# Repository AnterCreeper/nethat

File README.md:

# Dual Gigabit Ethernet HAT

If any questions, welcome for Issues & PRs   
如果有疑问，欢迎提交Issues或PR

**WARNING! This Project is not been fully productive tested, use at your own risk!**   
**警告！该项目未经充分的生产测试，使用需要你自己衡量**

### License

This project is licensed under the LGPL-2.1-or-later license. **DO NOT** download or clone this project until you have read and agree the LICENSE.     
该项目采用 `LGPL-2.1 以及之后版本` 授权。当你下载或克隆项目时，默认已经阅读并同意该协定。

### TODO
1. Should we add one EEPROM?

### Overview

This Project contains two `RTL8211F-CG` chips which is used to explore and demonstrate FPGA Ethernet application. This Project is compatible with [CUBE](https://github.com/AnterCreeper/CUBE) FPGA Devkit.  
该项目包含两个 `RTL8211F-CG` 芯片, 用于探索和展示基于 FPGA 的以太网应用。该项目与 [CUBE](https://github.com/AnterCreeper/CUBE) 开发工具搭配。

The PCB takes 4 layers JLC04161H-3313 Stacking, 1.6mm Thickness.
PCB 采用 4 层 JLC04161H-3313 叠层, 1.6mm 厚度。

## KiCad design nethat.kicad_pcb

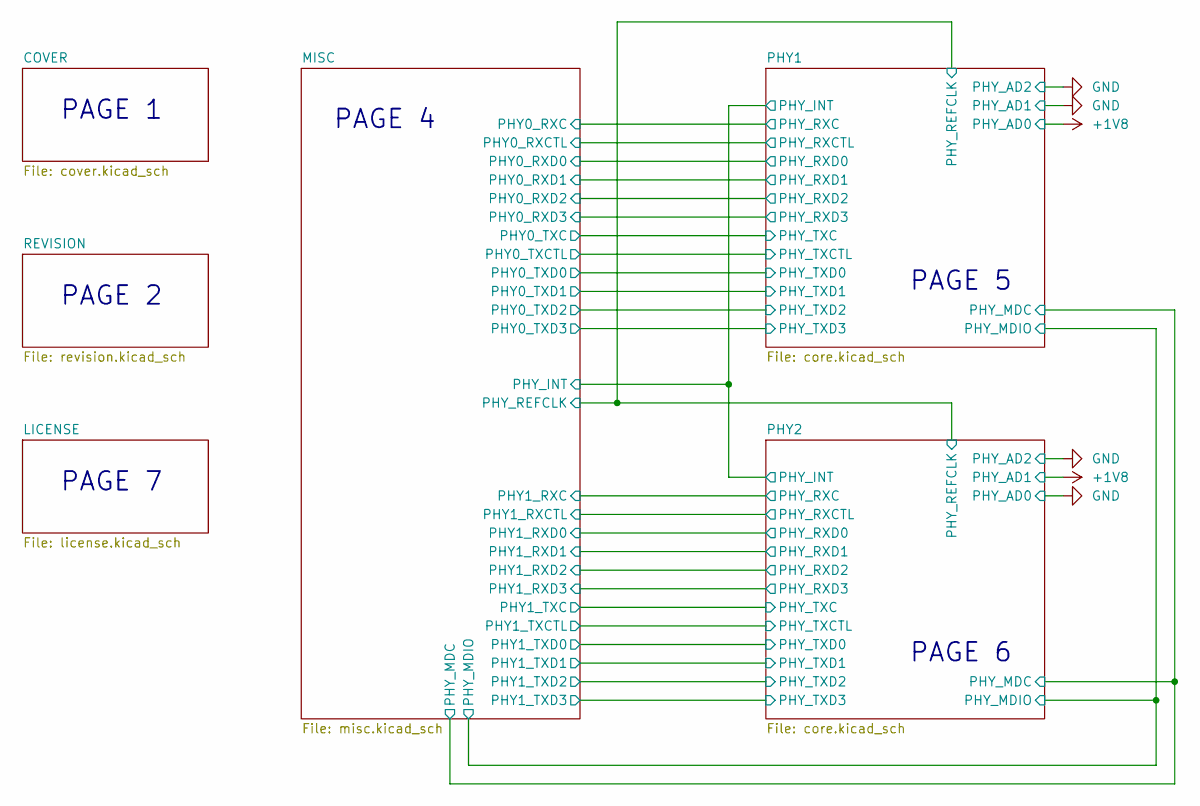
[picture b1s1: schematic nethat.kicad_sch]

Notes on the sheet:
PAGE 4
PAGE 1
PAGE 6
PAGE 2
PAGE 7
PAGE 5

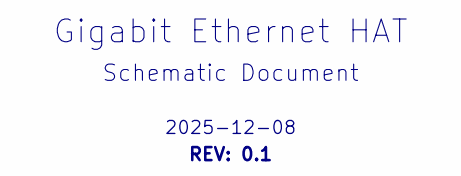
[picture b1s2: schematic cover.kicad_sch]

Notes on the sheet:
REV: 0.1
2025-12-08
Gigabit Ethernet HAT
Schematic Document

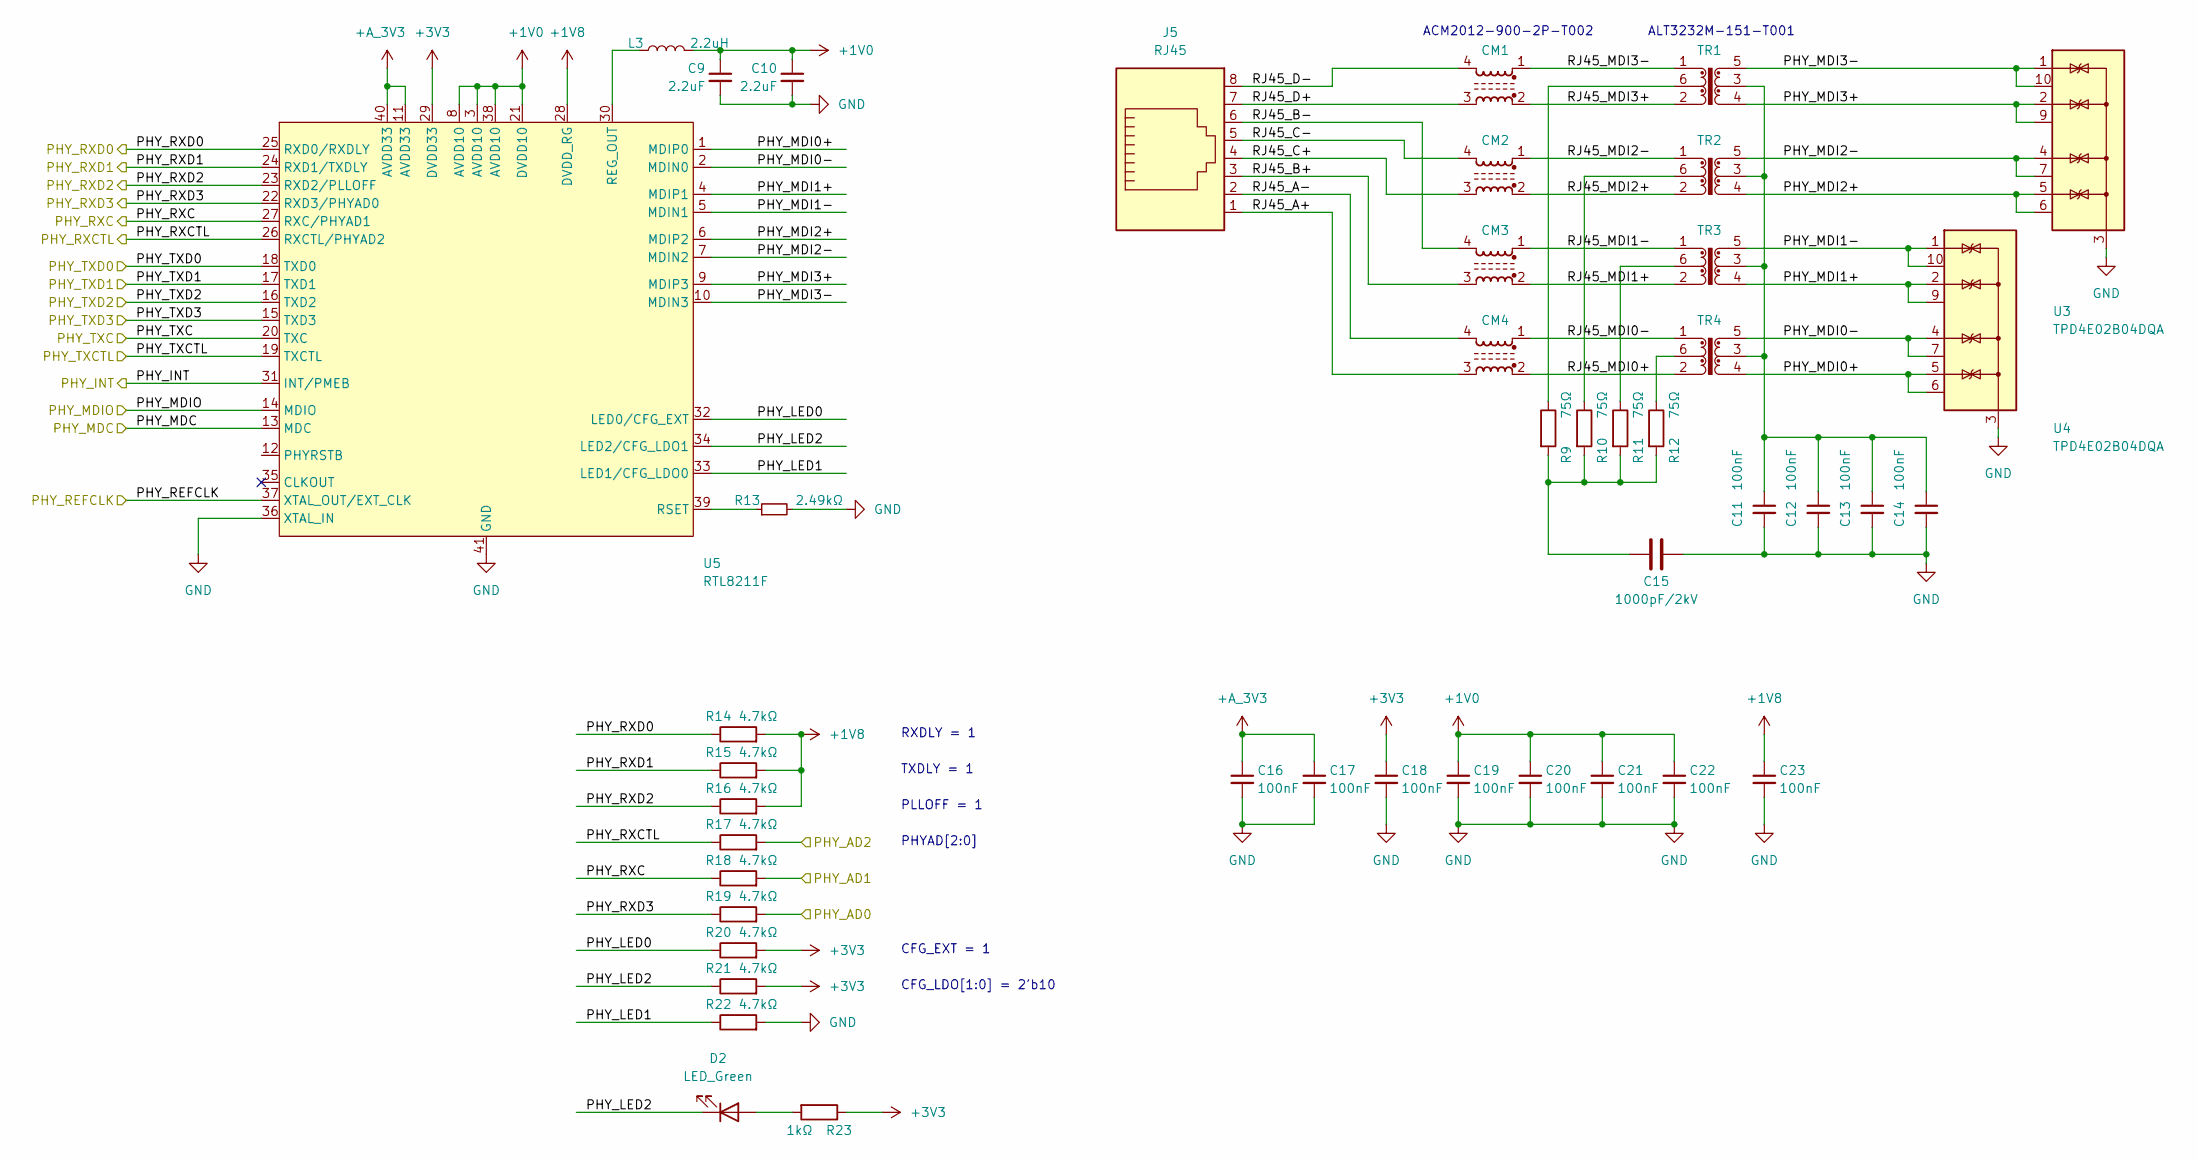
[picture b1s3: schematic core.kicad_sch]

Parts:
C9, C10: 2.2uF; C_0402_1005Metric
C11, C12, C13, C14, C16, C17, C18, C19, C20, C21, C22, C23: 100nF; C_0402_1005Metric
C15: 1000pF/2kV; C_1210_3225Metric
CM1, CM2, CM3, CM4: Choke_CommonMode_FerriteCore_1423; Filter_TDK_ACM2012-900-2P-T002
D2: LED_Green; LED_0603_1608Metric
J5: RJ45; RJ45_Wurth_615008150021
L3: 2.2uH; L_Murata_DFE201610P
R9, R10, R11, R12: 75Ω; R_0402_1005Metric
R13: 2.49kΩ; R_0402_1005Metric
R14, R15, R16, R17, R18, R19, R20, R21, R22: 4.7kΩ; R_0402_1005Metric
R23: 1kΩ; R_0402_1005Metric
TR1, TR2, TR3, TR4: TDK_ALT3232M_ALT4532M; Transformer_TDK_ALT3232M-151-T001
U3, U4: TPD4E02B04DQA; USON-10_2.5x1.0mm_P0.5mm
U5: RTL8211F; QFN-40-1EP_5x5mm_P0.4mm_EP3.8x3.8mm; LCSC Part C187932

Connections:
+1V0: C9.1, C10.1, C19.1, C20.1, C21.1, C22.1, L3.2, U5.3 (AVDD10), U5.8 (AVDD10), U5.21 (DVDD10), U5.38 (AVDD10); also elsewhere on the board
+1V8: C23.1, R14.2, R15.2, R16.2, R19.2, U5.28 (DVDD_RG); also elsewhere on the board
+3V3: C18.1, R20.2, R21.2, R23.1, U5.29 (DVDD33); also elsewhere on the board
+A_3V3: C16.1, C17.1, U5.11 (AVDD33), U5.40 (AVDD33); also elsewhere on the board
/MISC/PHY_INT: U5.31 (INT/PMEB); also elsewhere on the board
/MISC/PHY_MDC: U5.13 (MDC); also elsewhere on the board
/MISC/PHY_MDIO: U5.14 (MDIO); also elsewhere on the board
/PHY1/PHY_LED0: R20.1, U5.32 (LED0/CFG_EXT)
/PHY1/PHY_LED1: R22.1, U5.33 (LED1/CFG_LDO0)
/PHY1/PHY_LED2: D2.1 (K), R21.1, U5.34 (LED2/CFG_LDO1)
/PHY1/PHY_MDI0+: TR4.4, U4.5 (IO4), U4.6 (NC), U5.1 (MDIP0)
/PHY1/PHY_MDI0-: TR4.5, U4.4 (IO3), U4.7 (NC), U5.2 (MDIN0)
/PHY1/PHY_MDI1+: TR3.4, U4.2 (IO2), U4.9 (NC), U5.4 (MDIP1)
/PHY1/PHY_MDI1-: TR3.5, U4.1 (IO1), U4.10 (NC), U5.5 (MDIN1)
/PHY1/PHY_MDI2+: TR2.4, U3.5 (IO4), U3.6 (NC), U5.6 (MDIP2)
/PHY1/PHY_MDI2-: TR2.5, U3.4 (IO3), U3.7 (NC), U5.7 (MDIN2)
/PHY1/PHY_MDI3+: TR1.4, U3.2 (IO2), U3.9 (NC), U5.9 (MDIP3)
/PHY1/PHY_MDI3-: TR1.5, U3.1 (IO1), U3.10 (NC), U5.10 (MDIN3)
/PHY1/PHY_REFCLK: U5.37 (XTAL_OUT/EXT_CLK); also elsewhere on the board
/PHY1/PHY_RXC: R18.1, U5.27 (RXC/PHYAD1); also elsewhere on the board
/PHY1/PHY_RXCTL: R17.1, U5.26 (RXCTL/PHYAD2); also elsewhere on the board
/PHY1/PHY_RXD0: R14.1, U5.25 (RXD0/RXDLY); also elsewhere on the board
/PHY1/PHY_RXD1: R15.1, U5.24 (RXD1/TXDLY); also elsewhere on the board
/PHY1/PHY_RXD2: R16.1, U5.23 (RXD2/PLLOFF); also elsewhere on the board
/PHY1/PHY_RXD3: R19.1, U5.22 (RXD3/PHYAD0); also elsewhere on the board
/PHY1/PHY_TXC: U5.20 (TXC); also elsewhere on the board
/PHY1/PHY_TXCTL: U5.19 (TXCTL); also elsewhere on the board
/PHY1/PHY_TXD0: U5.18 (TXD0); also elsewhere on the board
/PHY1/PHY_TXD1: U5.17 (TXD1); also elsewhere on the board
/PHY1/PHY_TXD2: U5.16 (TXD2); also elsewhere on the board
/PHY1/PHY_TXD3: U5.15 (TXD3); also elsewhere on the board
/PHY1/RJ45_A+: CM4.3, J5.1
/PHY1/RJ45_A-: CM4.4, J5.2
/PHY1/RJ45_B+: CM3.3, J5.3
/PHY1/RJ45_B-: CM3.4, J5.6
/PHY1/RJ45_C+: CM2.3, J5.4
/PHY1/RJ45_C-: CM2.4, J5.5
/PHY1/RJ45_D+: CM1.3, J5.7
/PHY1/RJ45_D-: CM1.4, J5.8
/PHY1/RJ45_MDI0+: CM4.2, TR4.2
/PHY1/RJ45_MDI0-: CM4.1, TR4.1
/PHY1/RJ45_MDI1+: CM3.2, TR3.2
/PHY1/RJ45_MDI1-: CM3.1, TR3.1
/PHY1/RJ45_MDI2+: CM2.2, TR2.2
/PHY1/RJ45_MDI2-: CM2.1, TR2.1
/PHY1/RJ45_MDI3+: CM1.2, TR1.2
/PHY1/RJ45_MDI3-: CM1.1, TR1.1
GND: C9.2, C10.2, C11.2, C12.2, C13.2, C14.2, C15.2, C16.2, C17.2, C18.2, C19.2, C20.2, C21.2, C22.2, C23.2, R13.2, R17.2, R18.2, R22.2, U3.3 (G), U3.8 (G), U4.3 (G), U4.8 (G), U5.36 (XTAL_IN), U5.41 (GND); also elsewhere on the board
unnamed: C11.1, C12.1, C13.1, C14.1, TR1.3, TR2.3, TR3.3, TR4.3
unnamed: C15.1, R9.2, R10.2, R11.2, R12.2
unnamed: D2.2 (A), R23.2
unnamed: R9.1, TR1.6
unnamed: R10.1, TR2.6
unnamed: R11.1, TR3.6
unnamed: R12.1, TR4.6
unnamed: L3.1, U5.30 (REG_OUT)
unnamed: R13.1, U5.39 (RSET)

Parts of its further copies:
C24, C25: 2.2uF; C_0402_1005Metric
C26, C27, C28, C29, C31, C32, C33, C34, C35, C36, C37, C38: 100nF; C_0402_1005Metric
C30: 1000pF/2kV; C_1210_3225Metric
CM5, CM6, CM7, CM8: Choke_CommonMode_FerriteCore_1423; Filter_TDK_ACM2012-900-2P-T002
D3: LED_Green; LED_0603_1608Metric
J6: RJ45; RJ45_Wurth_615008150021
L4: 2.2uH; L_Murata_DFE201610P
R24, R25, R26, R27: 75Ω; R_0402_1005Metric
R28: 2.49kΩ; R_0402_1005Metric
R29, R30, R31, R32, R33, R34, R35, R36, R37: 4.7kΩ; R_0402_1005Metric
R38: 1kΩ; R_0402_1005Metric
TR5, TR6, TR7, TR8: TDK_ALT3232M_ALT4532M; Transformer_TDK_ALT3232M-151-T001
U6, U7: TPD4E02B04DQA; USON-10_2.5x1.0mm_P0.5mm
U8: RTL8211F; QFN-40-1EP_5x5mm_P0.4mm_EP3.8x3.8mm; LCSC Part C187932

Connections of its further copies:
+1V0: C24.1, C25.1, C34.1, C35.1, C36.1, C37.1, L4.2, U8.3 (AVDD10), U8.8 (AVDD10), U8.21 (DVDD10), U8.38 (AVDD10); also elsewhere on the board
+1V8: C38.1, R29.2, R30.2, R31.2, R33.2, U8.28 (DVDD_RG); also elsewhere on the board
+3V3: C33.1, R35.2, R36.2, R38.1, U8.29 (DVDD33); also elsewhere on the board
+A_3V3: C31.1, C32.1, U8.11 (AVDD33), U8.40 (AVDD33); also elsewhere on the board
/MISC/PHY_INT: U8.31 (INT/PMEB); also elsewhere on the board
/MISC/PHY_MDC: U8.13 (MDC); also elsewhere on the board
/MISC/PHY_MDIO: U8.14 (MDIO); also elsewhere on the board
/PHY1/PHY_REFCLK: U8.37 (XTAL_OUT/EXT_CLK); also elsewhere on the board
/PHY2/PHY_LED0: R35.1, U8.32 (LED0/CFG_EXT)
/PHY2/PHY_LED1: R37.1, U8.33 (LED1/CFG_LDO0)
/PHY2/PHY_LED2: D3.1 (K), R36.1, U8.34 (LED2/CFG_LDO1)
/PHY2/PHY_MDI0+: TR8.4, U7.5 (IO4), U7.6 (NC), U8.1 (MDIP0)
/PHY2/PHY_MDI0-: TR8.5, U7.4 (IO3), U7.7 (NC), U8.2 (MDIN0)
/PHY2/PHY_MDI1+: TR7.4, U7.2 (IO2), U7.9 (NC), U8.4 (MDIP1)
/PHY2/PHY_MDI1-: TR7.5, U7.1 (IO1), U7.10 (NC), U8.5 (MDIN1)
/PHY2/PHY_MDI2+: TR6.4, U6.5 (IO4), U6.6 (NC), U8.6 (MDIP2)
/PHY2/PHY_MDI2-: TR6.5, U6.4 (IO3), U6.7 (NC), U8.7 (MDIN2)
/PHY2/PHY_MDI3+: TR5.4, U6.2 (IO2), U6.9 (NC), U8.9 (MDIP3)
/PHY2/PHY_MDI3-: TR5.5, U6.1 (IO1), U6.10 (NC), U8.10 (MDIN3)
/PHY2/PHY_RXC: R33.1, U8.27 (RXC/PHYAD1); also elsewhere on the board
/PHY2/PHY_RXCTL: R32.1, U8.26 (RXCTL/PHYAD2); also elsewhere on the board
/PHY2/PHY_RXD0: R29.1, U8.25 (RXD0/RXDLY); also elsewhere on the board
/PHY2/PHY_RXD1: R30.1, U8.24 (RXD1/TXDLY); also elsewhere on the board
/PHY2/PHY_RXD2: R31.1, U8.23 (RXD2/PLLOFF); also elsewhere on the board
/PHY2/PHY_RXD3: R34.1, U8.22 (RXD3/PHYAD0); also elsewhere on the board
/PHY2/PHY_TXC: U8.20 (TXC); also elsewhere on the board
/PHY2/PHY_TXCTL: U8.19 (TXCTL); also elsewhere on the board
/PHY2/PHY_TXD0: U8.18 (TXD0); also elsewhere on the board
/PHY2/PHY_TXD1: U8.17 (TXD1); also elsewhere on the board
/PHY2/PHY_TXD2: U8.16 (TXD2); also elsewhere on the board
/PHY2/PHY_TXD3: U8.15 (TXD3); also elsewhere on the board
/PHY2/RJ45_A+: CM8.3, J6.1
/PHY2/RJ45_A-: CM8.4, J6.2
/PHY2/RJ45_B+: CM7.3, J6.3
/PHY2/RJ45_B-: CM7.4, J6.6
/PHY2/RJ45_C+: CM6.3, J6.4
/PHY2/RJ45_C-: CM6.4, J6.5
/PHY2/RJ45_D+: CM5.3, J6.7
/PHY2/RJ45_D-: CM5.4, J6.8
/PHY2/RJ45_MDI0+: CM8.2, TR8.2
/PHY2/RJ45_MDI0-: CM8.1, TR8.1
/PHY2/RJ45_MDI1+: CM7.2, TR7.2
/PHY2/RJ45_MDI1-: CM7.1, TR7.1
/PHY2/RJ45_MDI2+: CM6.2, TR6.2
/PHY2/RJ45_MDI2-: CM6.1, TR6.1
/PHY2/RJ45_MDI3+: CM5.2, TR5.2
/PHY2/RJ45_MDI3-: CM5.1, TR5.1
GND: C24.2, C25.2, C26.2, C27.2, C28.2, C29.2, C30.2, C31.2, C32.2, C33.2, C34.2, C35.2, C36.2, C37.2, C38.2, R28.2, R32.2, R34.2, R37.2, U6.3 (G), U6.8 (G), U7.3 (G), U7.8 (G), U8.36 (XTAL_IN), U8.41 (GND); also elsewhere on the board
unnamed: C26.1, C27.1, C28.1, C29.1, TR5.3, TR6.3, TR7.3, TR8.3
unnamed: C30.1, R24.2, R25.2, R26.2, R27.2
unnamed: D3.2 (A), R38.2
unnamed: R24.1, TR5.6
unnamed: R25.1, TR6.6
unnamed: R26.1, TR7.6
unnamed: R27.1, TR8.6
unnamed: L4.1, U8.30 (REG_OUT)
unnamed: R28.1, U8.39 (RSET)

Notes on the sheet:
ACM2012-900-2P-T002
PHYAD[2:0]
CFG_LDO[1:0] = 2'b10
CFG_EXT = 1
RXDLY = 1
PLLOFF = 1
ALT3232M-151-T001
TXDLY = 1

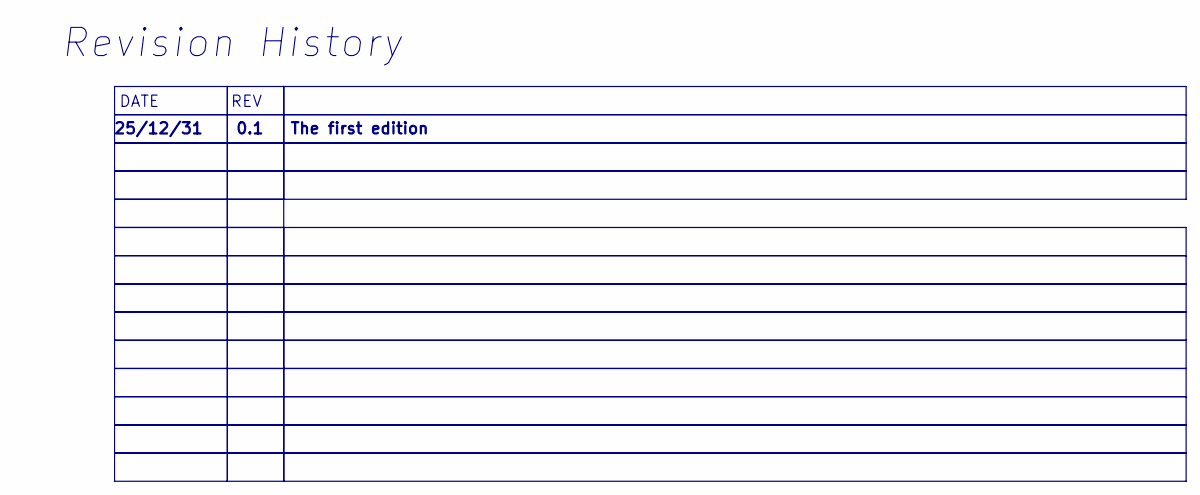
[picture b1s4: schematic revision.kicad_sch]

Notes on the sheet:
The first edition
Revision History
REV
25/12/31
0.1
DATE

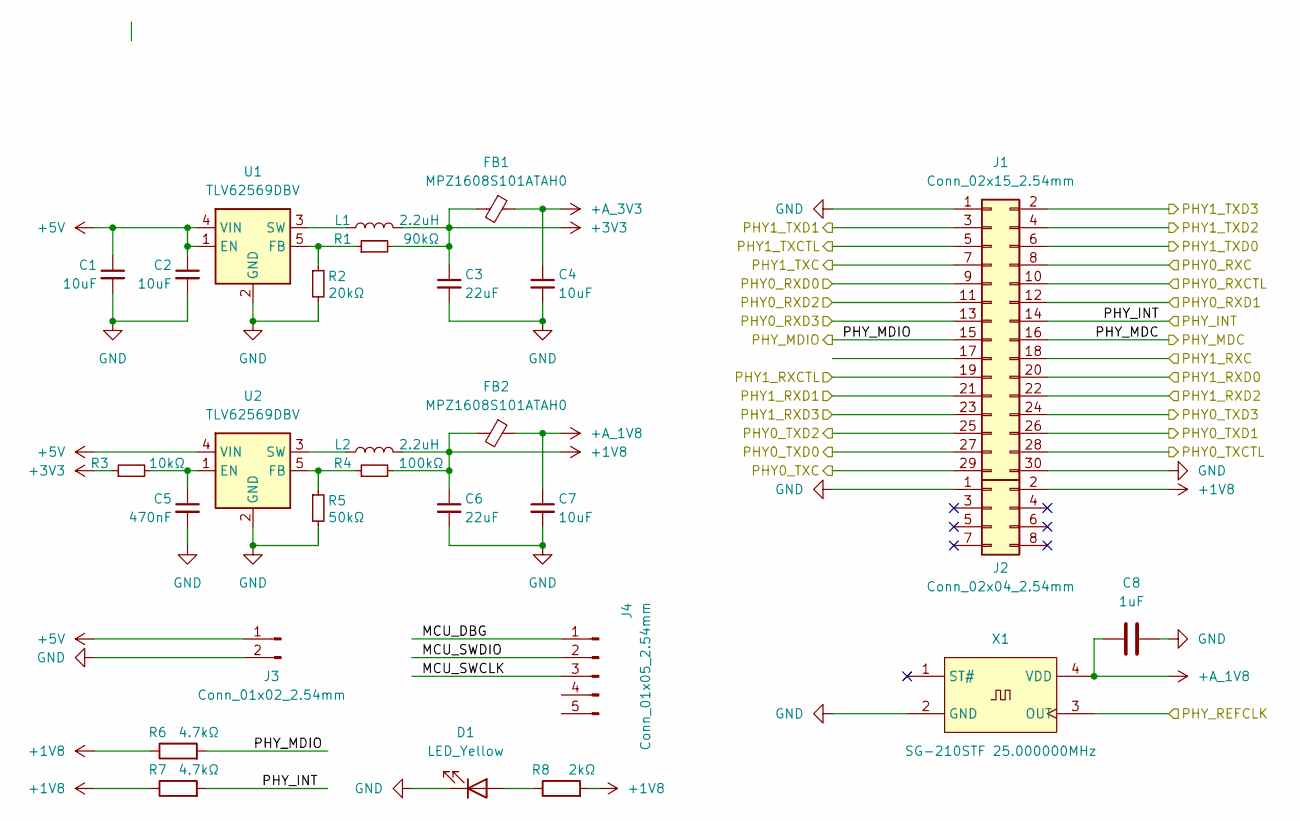
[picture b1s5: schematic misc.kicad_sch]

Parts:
C1, C2, C4, C7: 10uF; C_0603_1608Metric
C3, C6: 22uF; C_0603_1608Metric
C5: 470nF; C_0402_1005Metric
C8: 1uF; C_0402_1005Metric
D1: LED_Yellow; LED_0603_1608Metric
FB1, FB2: MPZ1608S101ATAH0; L_0603_1608Metric
J1: Conn_02x15_2.54mm; PinHeader_2x15_P2.54mm_Vertical
J2: Conn_02x04_2.54mm; PinHeader_2x04_P2.54mm_Vertical
J3: Conn_01x02_2.54mm; PinHeader_1x02_P2.54mm_Vertical
J4: Conn_01x05_2.54mm; PinHeader_1x05_P2.54mm_Vertical
L1, L2: 2.2uH; L_Murata_DFE201610P
R1: 90kΩ; R_0402_1005Metric
R2: 20kΩ; R_0402_1005Metric
R3: 10kΩ; R_0402_1005Metric
R4: 100kΩ; R_0402_1005Metric
R5: 50kΩ; R_0402_1005Metric
R6, R7: 4.7kΩ; R_0402_1005Metric
R8: 2kΩ; R_0402_1005Metric
U1, U2: TLV62569DBV; SOT-23-5
X1: SG-210STF 25.000000MHz; Oscillator_SMD_SeikoEpson_SG210-4Pin_2.5x2.0mm

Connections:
+1V8: C6.1, FB2.2, J2.2, L2.2, R4.2, R6.1, R7.1, R8.2; also elsewhere on the board
+3V3: C3.1, FB1.2, L1.2, R1.2, R3.1; also elsewhere on the board
+5V: C1.1, C2.1, J3.1, U1.1 (EN), U1.4 (VIN), U2.4 (VIN)
+A_1V8: C7.1, C8.1, FB2.1, X1.4 (VDD)
+A_3V3: C4.1, FB1.1; also elsewhere on the board
/MISC/MCU_DBG: J4.1
/MISC/MCU_SWCLK: J4.3
/MISC/MCU_SWDIO: J4.2
/MISC/PHY_INT: J1.14, R7.2; also elsewhere on the board
/MISC/PHY_MDC: J1.16; also elsewhere on the board
/MISC/PHY_MDIO: J1.15, R6.2; also elsewhere on the board
/PHY1/PHY_REFCLK: X1.3 (OUT); also elsewhere on the board
/PHY1/PHY_RXC: J1.8; also elsewhere on the board
/PHY1/PHY_RXCTL: J1.10; also elsewhere on the board
/PHY1/PHY_RXD0: J1.9; also elsewhere on the board
/PHY1/PHY_RXD1: J1.12; also elsewhere on the board
/PHY1/PHY_RXD2: J1.11; also elsewhere on the board
/PHY1/PHY_RXD3: J1.13; also elsewhere on the board
/PHY1/PHY_TXC: J1.29; also elsewhere on the board
/PHY1/PHY_TXCTL: J1.28; also elsewhere on the board
/PHY1/PHY_TXD0: J1.27; also elsewhere on the board
/PHY1/PHY_TXD1: J1.26; also elsewhere on the board
/PHY1/PHY_TXD2: J1.25; also elsewhere on the board
/PHY1/PHY_TXD3: J1.24; also elsewhere on the board
/PHY2/PHY_RXC: J1.18; also elsewhere on the board
/PHY2/PHY_RXCTL: J1.19; also elsewhere on the board
/PHY2/PHY_RXD0: J1.20; also elsewhere on the board
/PHY2/PHY_RXD1: J1.21; also elsewhere on the board
/PHY2/PHY_RXD2: J1.22; also elsewhere on the board
/PHY2/PHY_RXD3: J1.23; also elsewhere on the board
/PHY2/PHY_TXC: J1.7; also elsewhere on the board
/PHY2/PHY_TXCTL: J1.5; also elsewhere on the board
/PHY2/PHY_TXD0: J1.6; also elsewhere on the board
/PHY2/PHY_TXD1: J1.3; also elsewhere on the board
/PHY2/PHY_TXD2: J1.4; also elsewhere on the board
/PHY2/PHY_TXD3: J1.2; also elsewhere on the board
GND: C1.2, C2.2, C3.2, C4.2, C5.2, C6.2, C7.2, C8.2, D1.1 (K), J1.1, J1.30, J2.1, J3.2, R2.2, R5.2, U1.2 (GND), U2.2 (GND), X1.2 (GND); also elsewhere on the board
unnamed: D1.2 (A), R8.1
unnamed: R1.1, R2.1, U1.5 (FB)
unnamed: L1.1, U1.3 (SW)
unnamed: C5.1, R3.2, U2.1 (EN)
unnamed: R4.1, R5.1, U2.5 (FB)
unnamed: L2.1, U2.3 (SW)

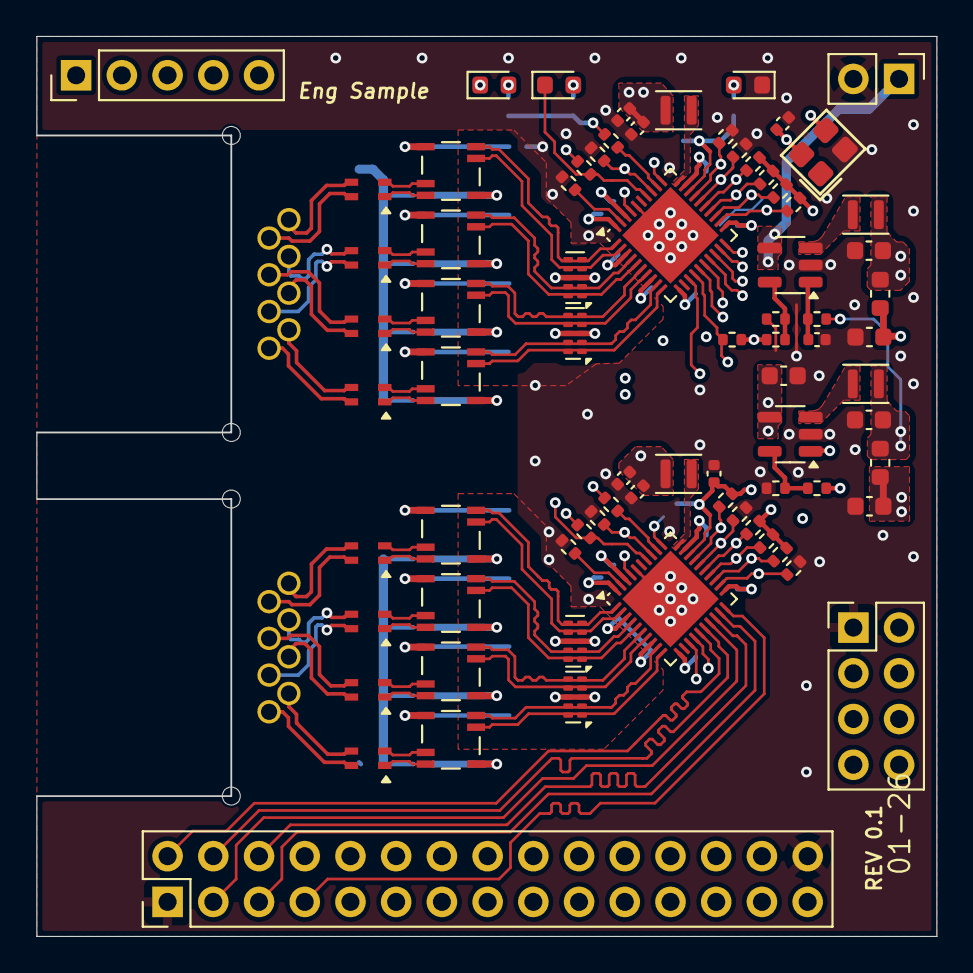
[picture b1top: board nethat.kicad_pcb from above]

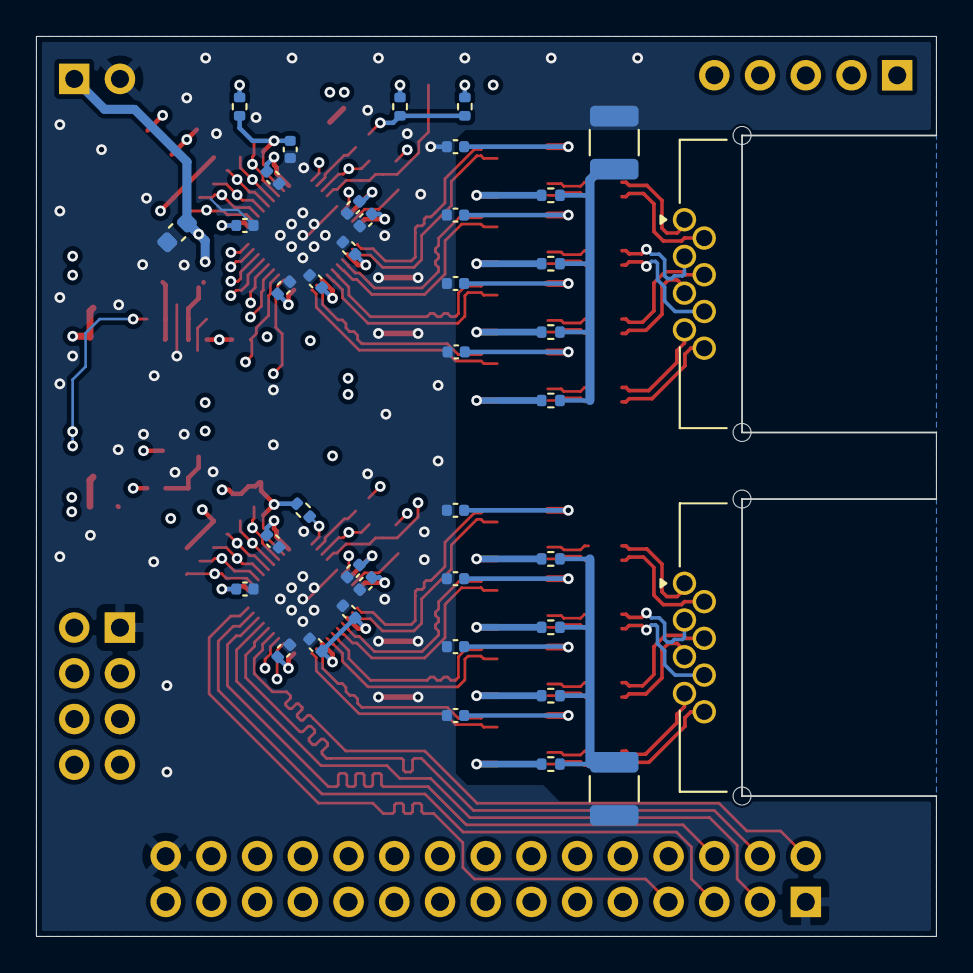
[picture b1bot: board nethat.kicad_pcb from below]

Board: 4 copper layers, 50.0 x 50.0 mm, 116 parts (40 on the bottom side), 113 nets.

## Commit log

2025-12-20 init project.
2025-12-22 update schematic.
2025-12-23 finish schematic.
2025-12-23 update schematic pdf and step models.
2025-12-29 update.
2025-12-30 first version release.
2025-12-31 first release v0.1
2025-12-31 tiny fixup.
